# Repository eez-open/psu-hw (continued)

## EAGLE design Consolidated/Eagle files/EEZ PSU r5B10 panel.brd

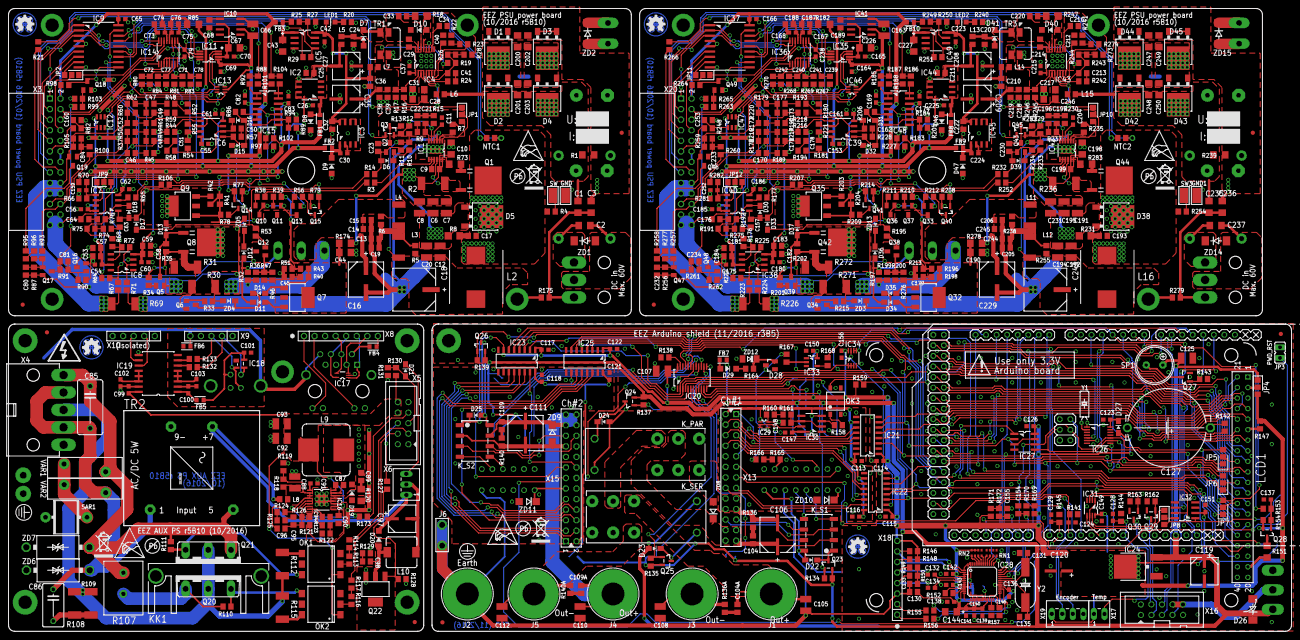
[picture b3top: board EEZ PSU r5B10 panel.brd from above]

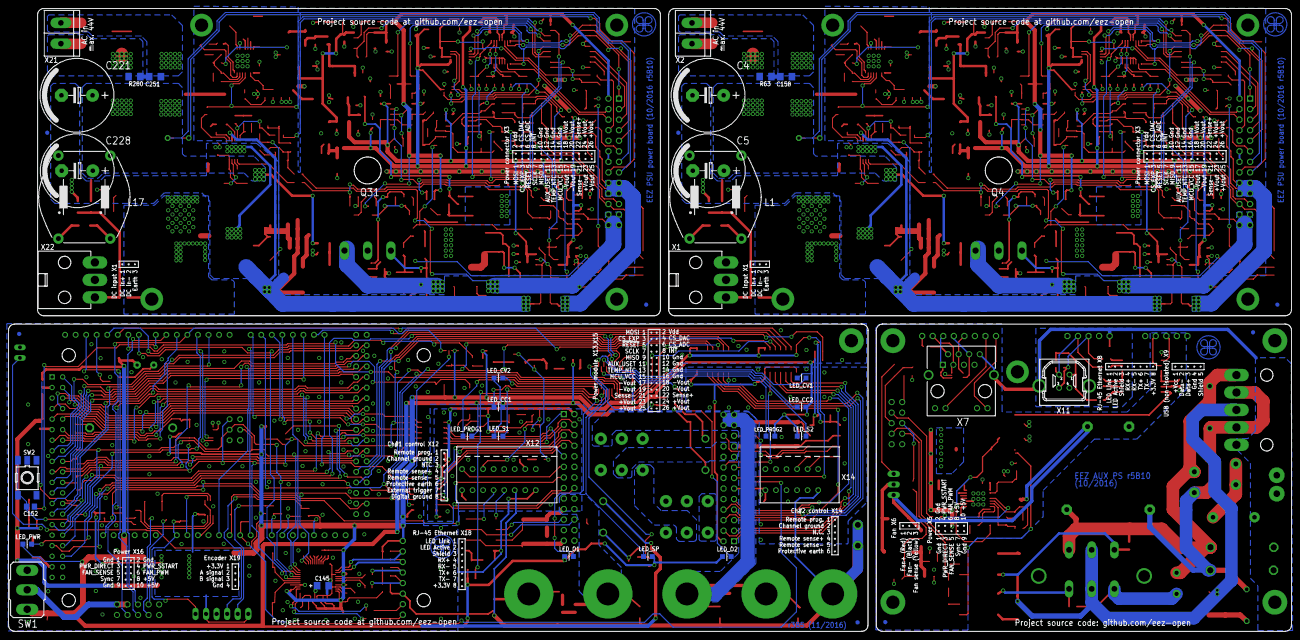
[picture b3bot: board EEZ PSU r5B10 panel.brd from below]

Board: 3 copper layers, 309.0 x 150.0 mm, 839 parts (32 on the bottom side), 579 nets.

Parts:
C1, C2, C3, C235, C236, C237: 4n7; C1206
C4, C5, C221, C228: 2m2; ECAP7.5/18
C6, C7, C8, C88, C92, C93, C191, C195, C231: 4u7; C1210
C9, C25, C32, C104, C109, C199, C211, C222: 470n; C0805
C10, C28, C31, C44, C190, C198, C217, C246: 1u/100V; C1206
C11, C26, C30, C37, C42, C54, C55, C56, C60, C61, C62, C65, C69, C70, C73, C75, C79, C82, C83, C91, C99, C100, C101, C102, C103, C113, C114, C115, C116, C117, C118, C121, C122, C123, C124, C126, C128, C129, C136, C137, C138, C139, C140, C141, C142, C143, C147, C149, C150, C151, C153, C156, C159, C161, C164, C165, C166, C167, C168, C169, C174, C175, C180, C185, C186, C204, C215, C223, C224, C225, C238, C252: 100n; C0603
C12, C20, C66, C107, C125, C163, C192, C194: 10u; C1210
C13, C57, C59, C68, C74, C76, C104A, C109A, C181, C183, C187, C188, C189, C244: 1u; C0805
C14, C15, C19, C39, C96, C160, C205, C206, C218, C245, C253: n.c.; C0805
C16, C229: EEEFK1J470P; CAPAE830X1050N
C17, C33, C89, C193, C220: 330p; C0805
C18, C243: EEEFK1J101P; PANASONIC_F
C21, C50, C162, C197: 120p; C0805
C22, C196: 4n7; C0805
C23, C230: 470p; C0805
C24, C36, C38, C207, C210, C219: 2u2; C0805
C27, C35, C119, C208, C209: 47u; CAPAE660X610N
C29, C87, C90, C130, C214: 22n; C0805
C34, C45, C53, C58, C80, C84, C133, C146, C154, C155, C179, C182, C184, C216, C232, C233: 10n; C0805
C40, C71, C72, C77, C78, C212, C239, C240, C241, C242: 3n3; C0805
C41, C63, C64, C94, C157, C176, C213: 1n; C0805
C43, C145, C227: 4u7; EC1206
C46, C52, C170, C172: 47p; C0805
C47, C48, C49, C51, C81, C171, C173, C177, C178, C234: 2n2; C0805
C67, C144, C226: 10u; EC1206
C85: 6n8 (X1); C102-064X133
C86: 47n/400V; C075-052X106
C95: 3n9; C0805
C97: 220u; CAPAE660X610N
C98, C148, C152: 47n; C0805
C105, C108, C110, C112: 4n7; C1210
C106, C111: EEEFK1J220P; CAPAE830X650N
C120: 10u; PANASONIC_C
C127: EECS5R5H105; SG-R20MM
C131, C135: 18p; C0805
C132, C134: 6n8; C0603
C158, C251: n.c; C1206
C200, C201, C202, C203, C247, C248, C249, C250: 1n; C1206
D1, D2, D3, D4, D42, D43, D44, D45: STPS15H100; TO252@1
D5, D38: STPS15H100; TO252
D6, D11, D12, D13, D14, D15, D16, D17, D18, D21, D22, D23, D24, D25, D27, D30, D31, D32, D33, D34, D35, D36, D37, D39: BAS316; SOD323-W
D7, D10, D19, D40, D41: DFLS1100-7; SOD123
D8, D9, D20, D29, D46, D47: SKL16; SOD123
D26: SMBJ5.0A-TR; DO214AA
D28: BAT54S; SOT23
EEZ_SIGNATURE, EEZ_SIGNATURE1, EEZ_SIGNATURE2, EEZ_SIGNATURE3: SIGNATURESMALL; SIGNATURE_5MM
FB1, FB2, FB3, FB4, FB5, FB6, FB7, FB8, FB9, FB10: 60R@100MHz; BEAD0603
FM1, FM2, FM3, FM4, FM5, FM6, FM7, FM8: FIDUCIAL_2; FIDUCIAL_DUAL
GND, GND1: S1751-46R
IC1, IC42: LTC3864EMSE#PBF; LTC_05-08-1666
IC2, IC44: MC79L05; SOIC127P600X173-8N
IC3, IC45: MC78L05; SOIC127P600X173-8N
IC4, IC43: LM5574MTX/NOPB; SOP65P640X110-16N
IC5, IC49: LP2951SO8; SOIC127P600X175-8N
IC6, IC7, IC39, IC40: TL072D; SOIC127P600X173-8N
IC8, IC38: OP27GSZ; SOIC127P600X173-8N
IC9, IC37: MCP23S08-E/SO; SOIC127P1030X265-18N
IC10, IC41: REF5025AIDG4; SOIC127P600X175-8N
IC11, IC35: DAC8552IDGKTG4; DGK8-M
IC12, IC47: ADG465SOT-23; SOT95P280X145-6N
IC13, IC46: TS5A9411DCKT; SOT65P210X110-6N
IC14, IC36: ADS1120IPWR; PW(R-PDSO-G16)
IC15, IC48: LP339D; SOIC127P600X175-14N
IC16: LM25575MH/NOPB; SOP65P640X110-17N
IC17: TPD4E002DRLR; SOT50P280X60-5N
IC18: TPD2E001DZDR; SOP192P292X122-4N
IC19: ADUM3160BRWZ; SOIC-16W
IC20: TLC5925IDBQR; SOP63P600X175-24N
IC21, IC25: Si8641EC-B-IS1; SOIC-16
IC22, IC23: SI8651EC-B-IS1; SOIC-16
IC24: LD1117ADT33TR; DPACK
IC26: PCA21125T/Q900/1,1; SOP65P640X120-14N
IC27: AT25256B-SSHL-B; SOIC127P600X175-8N
IC28: W5500; TQFP48-7X7
IC29: BC857BS; SOT65P210X110-6N
IC30: TLC555; SOIC127P600X175-8N
IC31: SN74LVC2G08DCTR; SOP65P400X130-8N
IC32: TPS3705-33D; SOIC127P600X175-8N
IC33: SN74LV1T34DBVR; SOT95P280X145-5N
IC34: SN74LVC2G02DCTR; SOP65P400X130-8N
J1, J4: BS-244DSM-R; BP_5_12
J2: BS-244DSM-G; BP_5_12
J3, J5: BS-244DSM-B; BP_5_12
J6: 1-726388-2; PCB_TAB-4.8MM
JP1, JP2, JP4, JP5, JP6, JP7, JP8, JP9, JP10, JP11, JP12: 0R-JUMPA; A0R-JMP
JP3: 901210762; JP1
KK1: SK 145/37,5; SK145
K_PAR: RT424005; RT-C/016A5_ROUND
K_S1, K_S2: G6K-2F-5DC; G6K-2F
K_SER: RT424005; RT-C/016A5_ROUND
L1, L17: RN114-4/02; RN114
L2, L16: 7443551331; WE-HCI_1350/1365
L3, L4, L11, L12: IHLP2020CZER3R3M11; IHLP-2020BZ-11
L5, L6, L7, L8, L13, L14, L15: 2u2; 0805
L9: 100uH; MSS1278
L10: 470u; DE0704
LCD1: TFT_320QVT; LCD_TFT_9341_MIRROR
LED1, LED2: HSMY-C170; LED_0805
LED_CC1, LED_CC2: HSMH-C170; LED_HSMH-C170
LED_CV1, LED_CV2: HSMY-C170; LED_0805
LED_O1, LED_O2: HSMG-C170; LED_0805
LED_PROG1, LED_PROG2: HSMH-C170; LED_HSMH-C170
LED_PWR: HSMD-C170; LED_0805
LED_S1, LED_S2: HSMY-C170; LED_0805
LED_SP: HSMH-C170; LED_HSMH-C170
MCU: Arduino Due; ARDUINO+ICSP_MIRROR
NTC1, NTC2: 10K/Beta:3570K; R_0204/5+0805
OK1: MOC3052; DIL6-SMD
OK2: MOC3062; DIL6-SMD
OK3: HCPL-181
Q1, Q44: IRFR5305; TO229P990X239-3N
Q2, Q10, Q11, Q17, Q36, Q37, Q43, Q47: MMBT5401; SOT23-BEC
Q3, Q15, Q27, Q29, Q30, Q40, Q45: 2N7002; SOT103P240X110-3N
Q4, Q31: IRFP250N; TO247BH-CLR
Q5, Q39: BC857C; SOT23-BEC
Q6, Q34: BC846C; SOT23-BEC
Q7, Q9, Q32, Q35: BCP56-16.115; SOT230P700X180-4N
Q8, Q42: IRFR5410; TO229P990X239-3N
Q12, Q13, Q16, Q18, Q19, Q33, Q38, Q46, Q48, Q49: MMBT5551; SOT23-BEC
Q14, Q41: BSS84P; SOT95P237X112-3N
Q20, Q21: BTA26-600; TOP3S-1
Q22: IRLL014N; SOT223
Q23, Q24, Q25, Q26, Q28: IRLML2246TRPBF; SOT95P237X112-3N
R1, R239: 12K; R1206
R2, R236: R010/2W; R2512
R3, R21, R57, R173, R228, R252, R266: 0R; R0805
R4, R33, R41, R74, R82, R95, R129, R167, R168, R204, R215, R248, R254, R258, R275: 1K; R0805
R5, R6, R43, R127, R164, R196, R238, R255: 100R; R0805
R7, R16, R19, R89, R90, R91, R103, R128, R162, R163, R205, R235, R243, R245, R261, R262, R265: 47K; R0805
R8, R18, R85, R120, R151, R174, R182, R231, R247, R278: 10R; R1206
R9, R10, R22, R23, R29, R45, R52, R54, R61, R75, R76, R78, R86, R98, R99, R106, R125, R131, R147, R153, R157, R170, R172, R180, R181, R189, R190, R191, R192, R206, R207, R209, R233, R237, R241, R251, R263, R264, R274: 10K; R0805
R11, R14, R77, R79, R143, R154, R208, R214, R232, R234: 100K; R0805
R12, R229: 330K; R0805
R13, R175, R253, R279: n.c.; R0805
R15, R102, R134, R135, R137, R139, R141, R144, R145, R169, R171, R183, R230: 4K7; R0805
R17, R32, R34, R35, R37, R46, R62, R65, R68, R94, R96, R110, R111, R119, R122, R124, R176, R177, R178, R179, R184, R197, R201, R202, R246, R276, R277: 2K2; R0805
R20, R40, R53, R195, R198, R240: 470R; R0805
R24, R51, R213, R242: 51K; R0805
R25, R36, R118, R123, R199, R249: 16K; R0805
R26, R92, R97, R104, R121, R130, R185, R186, R227, R244: 5K6; R0805
R27, R70, R88, R101, R165, R166, R187, R188, R250, R282: 5K1; R0805
R28, R56, R126, R138, R159, R212, R273: 1K8; R0805
R30, R271: R080/3W; R2512
R31, R272: 2R2/2W; R2512
R38, R39, R42, R48, R58, R66, R80, R81, R83, R84, R114, R117, R193, R194, R203, R210, R211, R267, R268, R269, R270, R281: 220R; R0805
R44, R55, R216, R221: 7K5 0.1%; R0805
R47, R93, R100, R160, R161, R200, R257, R260: 750R; R0805
R49, R59, R217, R218: 100K 0.1%; R0805
R50, R60, R219, R220: 22K 0.1%; R0805
R63, R280: n.c.; R1206
R64, R72, R222, R225: 2K55 0.1%; R0805
R67, R71, R223, R224: 102R 0.1%; R0805
R69, R226: R020/2W; R2512
R73, R283: 0...10R; R1206
R87, R105, R256, R259: 330R; R0805
R107: 18-22R/7W; R_0913
R108, R109, R112, R115: 330R/2W; R2512
R113, R116, R146, R148, R149, R150: 49R9; R0805
R132, R133: 22R; R0805
R136, R136A, R140, R140A: 1R; R0805
R142, R155, R156, R158: 180R; R0805
R152: 12K4; R0805
RN1, RN2: 4x10K; CAY16
SAR1: CG2-470L; SAR
SH1, SH4: Pgnd to Pout- short; SHORT_NOHOLE
SH2, SH5: Sgnd to Pgnd short; SHORT_NOHOLE
SH3: SHORT_NOHOLE
SP1: LD-BZEN-0903
SW, SW3: S1751-46R
SW1: A101SYCQ04; M9040P
SW2: 1301.9316; TACTM-6XN
TR1, TR3: SRF0703-821M; SRF0703
TR2: VTX-214-005-112 (or MYRRA 47154); PCB_ACDC_MYRRA_5W
U$1, U$2, U$8, U$11: RECYCLE_BIN1/8
U$3, U$5, U$9, U$12: PB_SMALL
U$4, U$6, U$7, U$10: ESD_SYMBOL
VAR1, VAR2: S20K250; VARISTOR
X1, X22: 39303035; MINIFIT_6659-3
X2, X21: 282836-2; TBLOCK5.0_2
X3, X20: SSW-113-02-T-D-RA
X4: 39303055; MINIFIT_6659-5
X5, X16: 09185067324; IDC-10PIN
X6: 22-23-2031
X7: LMJ2138814S0L1T1C; RJ45-VERT
X8: 826629-8; SSW-108-02-S-S
X9, X10: 826629-5; SSW-105-02-S-S
X11: 2411-01; KUSBVX-BS1N
X12: MC000006; MC000006_MIRROR
X13, X15: TSW-113-07-F-D
X14: MC000005; MC000005_MIRROR
X17: 22-23-2021
X18: MC34753; SSW-108-02-S-S
X19: 22-23-2041
Y1: 32,768kHz; R26_XTAL
Y2: 25MHz; HC-49/4H
ZD1, ZD2, ZD14, ZD15: n.c.; DO214AA
ZD3, ZD4: BZX384-C15.115; SOD323-W
ZD5, ZD13: PDZ6.2B; SOD323-W
ZD6, ZD7: 1.5KE400CA; DO201-BIDIR
ZD8, ZD9: P4SMAJ48A; DO214AC
ZD10, ZD11: SMAJ18A; DO214AC
ZD12: 4V3; MINIMELF

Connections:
1V2O: C146.2, IC28.22
!ADC1_SELECT: IC22.4, MCU.15
!ADC2_SELECT: IC25.4, MCU.48
!BP_OE: IC20.21, MCU.10
!BP_OUT0: IC20.5, LED_CV1.C
!BP_OUT1: IC20.6, Q23.1, R134.1
!BP_OUT2: IC20.7, LED_O1.C
!BP_OUT3: IC20.8, LED_SP.C
!BP_OUT4: IC20.9, LED_PROG1.C
!BP_OUT5: IC20.10, LED_S1.C
!BP_OUT6: IC20.11, LED_CC1.C
!BP_OUT7: IC20.12, LED_CV2.C
!BP_OUT8: IC20.13, Q25.1, R135.1
!BP_OUT9: IC20.14, Q24.1, R137.1
!BP_OUT10: IC20.15, LED_CC2.C
!BP_OUT12: IC20.17, LED_S2.C
!BP_OUT13: IC20.18, LED_O2.C
!BP_OUT14: IC20.19, Q26.1, R139.1
!BP_OUT15: IC20.20, LED_PWR.C
!CH1_ADC: IC22.13, X13.6
!CH1_DAC: IC21.12, X13.4
!CH1_EXPANDER: IC21.13, X13.3
!CH1_INT: IC22.11, X13.8
!CH1_RESET: IC22.14, X13.5
!CH2_ADC: IC25.13, X15.6
!CH2_DAC: IC23.12, X15.4
!CH2_EXPANDER: IC23.13, X15.3
!CH2_INT: IC23.11, X15.8
!CH2_RESET: IC25.14, X15.5
!CONVEND1: IC22.6, MCU.21
!CONVEND2: IC23.6, MCU.20
!DAC1_SELECT: IC21.5, MCU.16
!DAC2_SELECT: IC23.5, MCU.47
!DP_DRIVE: Q9.1, R41.1, R78.1
!DP_DRIVE1: Q35.1, R204.1, R209.1
!EEPROM_SELECT: IC27.1, MCU.49
!ETH_IRQ: IC28.36, MCU.18
!ETH_SELECT: IC28.32, MCU.11
!INT: JP2.2, X3.8
!INT1: JP11.2, X20.8
!IO_EXPANDER1: IC21.4, MCU.17
!IO_EXPANDER2: IC23.4, MCU.46
!MR: C152.2, IC32.1, JP8.1, SW2.3, SW2.4
!PS_DRDY: IC14.14, JP2.3
!PS_DRDY1: IC36.14, JP11.3
!PS_RESET: IC9.6, X3.5
!PS_RESET1: IC37.6, X20.5
!RESET: IC22.3, IC25.3, IC28.37, IC32.7, MCU.RESET
!RESET1: IC31.1, IC31.6, JP8.3
!RTC_IRQ: IC26.5, MCU.19
!SET_100%: IC9.13, Q3.1
!SET_100%1: IC37.13, Q45.1
!SET_DP: IC9.11, Q14.1, R77.2
!SET_DP1: IC37.11, Q41.1, R214.2
+3V3: C107.1, C114.1, C115.1, C117.1, C120.1, C122.1, C126.1, C130.1, C136.2, C138.1, C139.1, C140.1, C141.1, C142.1, C143.1, C144.+, C149.2, C150.1, C151.2, C156.1, D27.A, IC20.24, IC21.1, IC22.1, IC22.7, IC23.1, IC23.7, IC24.4, IC25.1, IC27.3, IC27.7, IC27.8, IC28.4, IC28.8, IC28.11, IC28.15, IC28.17, IC28.21, IC28.28, IC31.8, IC32.2, IC33.5, IC34.8, JP4.3, Q28.2, R146.1, R147.2, R148.2, R154.2, R159.1, R169.1, R171.1, RN2.6, RN2.7, RN2.8, X13.15, X15.15, X17.1, X18.8, X19.1
+5V: C65.1, C73.2, C74.2, C92.1, C93.1, C99.1, FB3.P$2, IC9.18, IC14.13, IC16.11, IC19.16, L9.2, OK1.1, OK2.1, Q13.B, Q14.2, R77.1, R88.2, R98.2, R101.2, R121.1, R130.1, X3.2, X5.8, X5.10
+5V1: C166.1, C168.2, C188.2, FB10.P$2, IC36.13, IC37.18, Q33.B, Q41.2, R187.2, R188.2, R214.1, R264.2, X20.2
+5V2: C119.1, C125.2, D26.C, FB7.P$1, IC24.3, JP4.1, LED_CC1.A, LED_CC2.A, LED_CV1.A, LED_CV2.A, LED_O1.A, LED_O2.A, LED_PROG1.A, LED_PROG2.A, LED_PWR.A, LED_S1.A, LED_S2.A, LED_SP.A, MCU.5V, Q23.2, Q24.2, Q25.2, Q26.2, R134.2, R135.2, R137.2, R139.2, SP1.+B, SW1.3
+VNR: C32.1, C36.1, C42.1, IC3.8, IC5.8, L7.2, LED1.A
+VNR1: C210.1, C222.1, C223.1, IC45.8, IC49.8, L14.2, LED2.A
+VREF: C67.+, C70.2, C79.2, IC10.6, IC11.2, IC14.9, R70.1
+VREF1: C165.2, C226.+, C238.2, IC35.2, IC36.9, IC41.6, R282.1
-9V: C25.2, C27.2, IC2.2, IC2.3, IC2.6, IC2.7, L5.2, R41.2, R42.2
-9V1: C208.2, C211.2, IC44.2, IC44.3, IC44.6, IC44.7, L13.2, R203.2, R204.2
AC_EARTH: FB6.P$1, SAR1.P$2, X4.5, X7.8, X7.SH1, X7.SH2, X9.5, X11.M1, X11.M2, ZD6.C, ZD7.C
AC_IN1: C202.1, C203.2, D3.3, D4.1, D4.2, R63.2, X2.1, ZD2.A
AC_IN1_MAIN: C85.1, Q21.A1, R107.1, R111.2, TR2.5, VAR1.P$2, X4.1, ZD7.A
AC_IN2: C158.1, C200.1, C201.2, D1.3, D2.1, D2.2, X2.2, ZD2.C
AC_IN2_MAIN: C85.2, C86.1, TR2.1, VAR2.P$1, X4.2, X4.4, ZD6.A
AC_IN3: C247.1, C248.2, C251.1, D42.1, D42.2, D44.3, X21.2, ZD15.C
AC_IN4: C249.1, C250.2, D43.1, D43.2, D45.3, R280.2, X21.1, ZD15.A
AUX1_USET_IN: X12.8, X12.8.1, X13.11, ZD10.C
AUX2_USET_IN: X14.6, X14.6.1, X15.11, ZD11.C
AUX_+3V3: FB4.P$2, X8.8
AUX_ETH_ACTLED: X7.10, X8.2
AUX_ETH_IN+: IC17.4, X7.4, X8.4
AUX_ETH_IN-: IC17.5, X7.6, X8.5
AUX_ETH_LINKLED: X7.12, X8.1
AUX_ETH_OUT+: IC17.1, X7.1, X8.6
AUX_ETH_OUT-: IC17.3, X7.3, X8.7
AUX_FAN_CTRL: R127.2, X5.6
AUX_FAN_SENSE: D21.A, R130.2, R131.1, X5.5
AUX_PWR_DIRECT: R114.2, X5.3
AUX_PWR_SSTART: R117.2, X5.4
AUX_USET_IN: R82.2, X3.11
AUX_USET_IN1: R248.2, X20.11
AUX_USET_SW: IC9.14, IC13.1
AUX_USET_SW1: IC37.14, IC46.1
BATT_NTC: MCU.A4, OK3.4, R159.2
BP_SELECT: IC20.4, MCU.9
BUZZER: MCU.12, Q27.1, R143.2
CC_ACTIVE: IC9.12, R101.1, R104.2
CC_ACTIVE1: IC37.12, R186.2, R188.1
CH1_GND: C113.2, C116.2, C147.2, C148.1, IC21.9, IC21.15, IC22.9, IC30.1, OK3.2, X12.7, X12.7.1, X13.10, X13.12, X13.14, ZD10.A
CH1_MISO: IC21.11, X13.9
CH1_MOSI: IC21.14, X13.1
CH1_SCLK: IC22.12, X13.7
CH1_SYNC: IC22.15, X13.16
CH1_VDD: C113.1, C116.1, C147.1, IC21.10, IC21.16, IC22.10, IC22.16, IC29.1, IC29.4, IC30.4, IC30.8, X13.2
CH2_GND: C118.2, C121.2, IC23.9, IC25.9, IC25.15, X14.5, X14.5.1, X15.10, X15.12, X15.14, ZD11.A
CH2_MISO: IC25.11, X15.9
CH2_MOSI: IC23.14, X15.1
CH2_SCLK: IC25.12, X15.7
CH2_SYNC: IC23.15, X15.16
CH2_VDD: C118.1, C121.1, IC23.10, IC23.16, IC25.10, IC25.16, X15.2
CS_ADC: IC14.2, X3.6
CS_ADC1: IC36.2, X20.6
CS_DAC: IC11.5, X3.4
CS_DAC1: IC35.5, X20.4
CS_EXPANDER: IC9.7, X3.3
CS_EXPANDER1: IC37.7, X20.3
CV_ACTIVE: IC9.15, R88.1, R92.2
CV_ACTIVE1: IC37.15, R185.2, R187.1
D+: IC18.2, R133.1, X9.3, X11.3
D-: IC18.3, R132.1, X9.2, X11.2
DC+: C2.2, L1.2, X1.1, ZD1.C
DC+1: C237.2, L17.2, X22.1, ZD14.C
DC-: C2.1, L1.1, X1.2, ZD1.A
DC-1: C237.1, L17.1, X22.2, ZD14.A
DC_BIAS: C44.1, Q7.2, Q7.4, R38.2, R39.2, R174.2
DC_BIAS1: C190.1, Q32.2, Q32.4, R210.2, R211.2, R278.2
DC_OUT: C1.2, C4.+, C5.+, C6.1, C7.1, C8.1, C9.2, C10.1, C201.1, C203.1, D2.3, D4.3, IC1.11, L1.3, L6.1, R1.1, R2.1, R174.1
DC_OUT1: C191.1, C195.1, C198.1, C199.2, C221.+, C228.+, C231.1, C235.2, C248.1, C250.1, D42.3, D43.3, IC42.11, L15.1, L17.3, R236.1, R239.1, R278.1
DC_PREG1: C28.1, C31.1, IC4.3, L6.2, R16.2
DC_PREG2: C88.1, IC16.3, L8.2, R118.2
DC_PREG3: C217.1, C246.1, IC43.3, L15.2, R245.2
DP_LED: Q14.3, R78.2
DP_LED1: Q41.3, R209.2
EARTH: C1.1, C3.2, R175.2, X1.3
EARTH1: C235.1, C236.2, R279.2, X22.3
EARTH2: C105.2, C108.1, C110.2, C112.1, C130.2, C133.2, J2.P$1, J6.P$1, J6.P$2, X12.3, X12.3.1, X14.1, X14.1.1, X18.3
ENC_A: C154.2, MCU.A8, R170.1
ENC_B: C155.1, MCU.A9, R172.1
ETH_ACTLED: IC28.27, R155.1
ETH_IN+: C134.1, R150.1, X18.4
ETH_IN-: C132.1, R149.2, X18.5
ETH_LINKLED: IC28.25, R156.1
ETH_OUT+: IC28.2, R148.1, X18.6
ETH_OUT-: IC28.1, R146.2, X18.7
EXT_TRIG: MCU.A7, R168.1
FAN_OUT: C98.2, D20.A, L10.2, Q22.2, Q22.4
FAN_PWM: MCU.6, X16.6
FAN_SENSE: MCU.13, X16.5
FB: IC1.5, Q3.2, R12.2, R13.2, R15.1
FB1: IC42.5, Q45.2, R229.2, R230.1, R253.2
GCOM: JP9.2, R44.1, R64.1
GCOM1: JP12.2, R216.1, R222.1
GND: C3.1, C4.-, C5.-, C6.2, C7.2, C8.2, C10.2, C12.2, C18.2, C20.2, C24.2, C25.1, C26.1, C27.1, C28.2, C30.2, C31.2, C32.2, C34.2, C35.2, C36.2, C37.1, C38.2, C39.2, C40.1, C42.2, C43.-, C44.2, C45.2, C53.1, C54.2, C55.1, C56.1, C57.1, C58.1, C59.1, C60.2, C61.1, C62.1, C65.2, C66.2, C67.-, C68.2, C69.1, C70.1, C71.1, C72.2, C73.1, C74.1, C75.1, C76.1, C77.1, C78.1, C79.1, C82.1, C83.1, C88.2, C90.2, C91.1, C92.2, C93.2, C94.1, C99.2, C102.2, C159.2, C160.1, C200.2, C202.2, D1.1, D1.2, D3.1, D3.2, D5.1, D5.2, D8.C, D9.A, GND.P$1, IC1.TP, IC2.5, IC3.2, IC3.3, IC3.6, IC3.7, IC4.9, IC4.12, IC5.4, IC9.4, IC9.5, IC9.9, IC10.4, IC11.8, IC13.3, IC14.3, IC14.4, IC14.5, IC14.8, IC16.9, IC16.12, IC16.TP, IC17.2, IC19.9, IC19.15, JP9.3, L1.4, Q8.2, Q15.2, Q16.E, Q18.E, Q22.3, R1.2, R8.1, R17.1, R20.2, R22.2, R27.2, R28.1, R46.1, R47.1, R51.1, R66.2, R79.1, R90.1, R94.1, R97.2, R103.1, R119.1, R122.2, R126.2, R128.1, R129.1, R131.2, SH1.P$2, SH2.P$2, TR1.4, TR2.9, X3.10, X3.12, X3.14, X5.1, X5.2, X5.9, X7.9, X7.11, X10.4
GND1: C153.1, C161.1, C163.2, C164.1, C165.1, C166.2, C167.1, C168.1, C169.1, C174.1, C175.2, C179.2, C180.2, C181.1, C182.1, C183.1, C184.1, C185.1, C186.1, C187.1, C188.1, C189.2, C190.2, C191.2, C192.2, C194.2, C195.2, C198.2, C207.2, C208.1, C209.2, C210.2, C211.1, C212.1, C215.1, C216.2, C217.2, C218.2, C219.2, C221.-, C222.2, C223.2, C224.2, C225.1, C226.-, C227.-, C228.-, C231.2, C236.1, C238.1, C239.1, C240.1, C241.1, C242.2, C243.2, C246.2, C247.2, C249.2, C252.2, C253.1, D38.1, D38.2, D44.1, D44.2, D45.1, D45.2, D46.C, D47.A, GND1.P$1, IC35.8, IC36.3, IC36.4, IC36.5, IC36.8, IC37.4, IC37.5, IC37.9, IC41.4, IC42.TP, IC43.9, IC43.12, IC44.5, IC45.2, IC45.3, IC45.6, IC45.7, IC46.3, IC49.4, JP12.3, L17.4, Q40.2, Q42.2, Q48.E, Q49.E, R184.1, R200.1, R208.1, R213.1, R227.2, R231.1, R239.2, R240.2, R241.2, R246.1, R250.2, R262.1, R265.1, R273.1, R276.1, R281.2, SH4.P$2, SH5.P$2, TR3.4, X20.10, X20.12, X20.14
GND7: C107.2, C114.2, C115.2, C117.2, C119.2, C120.2, C122.2, C123.1, C124.1, C125.1, C126.2, C127.2, C128.1, C129.1, C131.2, C135.2, C136.1, C137.1, C138.2, C139.2, C140.2, C141.2, C142.2, C143.2, C144.-, C146.1, C149.1, C150.2, C151.1, C152.1, C154.1, C155.2, C156.2, D22.A, D23.A, D24.A, D25.A, D26.A, D28.1, IC20.1, IC21.2, IC21.8, IC22.8, IC23.8, IC24.1, IC25.2, IC25.8, IC26.7, IC27.4, IC28.29, IC31.4, IC32.3, IC32.4, IC33.3, IC34.4, JP3.2, K_PAR.A1, K_S1.8, K_S2.8, K_SER.A1, LCD1.1, MCU.GND, MCU.GND1, MCU.GND2, MCU.GND3, MCU.GND4, MCU.ICSP_GND, OK3.3, Q27.2, Q29.2, Q30.2, R138.1, R141.2, R143.1, R144.2, R145.2, R157.1, R162.2, R163.2, RN1.5, RN1.6, RN1.7, RN1.8, RN2.5, SH3.P$1, SW2.1, SW2.2, SW2.5, X12.1, X12.1.1, X16.1, X16.2, X16.9, X19.4, ZD12.A
GNDA: C145.-, IC28.3, IC28.9, IC28.14, IC28.16, IC28.19, IC28.48, R152.1, SH3.P$2
INT_EXP: IC9.8, JP2.1
INT_EXP1: IC37.8, JP11.1
IS: D10.A, IC4.13, R18.1
IS1: D19.A, IC16.13, R120.1
IS2: D40.A, IC43.13, R247.1
ISENSE+: IC8.3, R64.2, R67.2
ISENSE+1: IC38.3, R222.2, R223.2
ISENSE-: IC8.2, R71.2, R72.1
ISENSE-1: IC38.2, R224.2, R225.1
ISOLATOR1_EN: IC21.7, MCU.14
ISOLATOR2_EN: IC25.7, MCU.45
I_MON: IC8.6, R68.1, R72.2, R84.1
I_MON1: IC38.6, R176.1, R225.2, R268.1
I_SERVO: C63.2, D17.C, D18.A, IC7.1, R106.1
I_SERVO1: C157.2, D30.A, D33.C, IC40.1, R207.1
I_SET: IC11.3, R65.1, R80.1
I_SET1: IC35.3, R177.1, R270.1
LCDSD_CS: LCD1.38, MCU.53
LCD_BRIGHTNESS: MCU.7, R153.1
LCD_CS: LCD1.15, MCU.39
LCD_DB0: LCD1.21, MCU.37
LCD_DB1: LCD1.22, MCU.36
LCD_DB2: LCD1.23, MCU.35
LCD_DB3: LCD1.24, MCU.34
LCD_DB4: LCD1.25, MCU.33
LCD_DB5: LCD1.26, MCU.32
LCD_DB6: LCD1.27, MCU.31
LCD_DB7: LCD1.28, MCU.30
LCD_DB8: LCD1.7, MCU.22
LCD_DB9: LCD1.8, MCU.23
LCD_DB10: LCD1.9, MCU.24
LCD_DB11: LCD1.10, MCU.25
LCD_DB12: LCD1.11, MCU.26
LCD_DB13: LCD1.12, MCU.27
LCD_DB14: LCD1.13, MCU.28
LCD_DB15: LCD1.14, MCU.29
LCD_RD: LCD1.6, R147.1
LCD_RESET: LCD1.17, MCU.38
LCD_RS: LCD1.4, MCU.41
LCD_WR: LCD1.5, MCU.40
LED_A: LCD1.19, R151.2
L_OUT: C12.1, C18.1, C20.1, L2.2, L3.1, R5.1, R10.1, R11.1, R12.1
L_OUT12: C192.1, C194.1, C243.1, L12.1, L16.2, R229.1, R233.1, R234.1, R255.1
MCU_D+: IC19.10, X10.3
MCU_D-: IC19.11, X10.2
MCU_VCC: NTC1.2, NTC1.2.1, X3.15
MCU_VCC1: NTC2.2, NTC2.2.1, X20.15
MISO: IC21.6, IC25.6, IC26.8, IC27.2, IC28.34, JP7.1, LCD1.35, MCU.ICSP_MISO
MODE: IC1.1, JP1.2
MODE1: IC42.1, JP10.2
MOSI: IC20.2, IC21.3, IC23.3, IC26.9, IC27.5, IC28.35, JP6.1, LCD1.37, MCU.ICSP_MOSI
unnamed: Q9.3, R42.1
unnamed: Q5.B, R34.2
unnamed: C46.2, R45.1
unnamed: C26.2, D8.A, FB1.P$1, IC2.1
unnamed: C30.1, D9.C, FB2.P$1, IC3.1
unnamed: C43.+, FB3.P$1, IC5.1, R25.1, R29.1
unnamed: R4.2, SW.P$1
unnamed: R74.2, R75.1
unnamed: IC12.4, IC13.6
unnamed: C52.2, R61.1
unnamed: C68.1, IC10.5
unnamed: C160.2, IC12.1, R82.1
unnamed: C63.1, R74.1
unnamed: C158.2, R63.1
unnamed: C159.1, IC7.5, R66.1, R70.2
unnamed: IC7.6, IC7.7, JP9.1
unnamed: C49.1, R59.2, R60.1
unnamed: C50.2, R57.1
unnamed: D6.C, Q2.E, R10.2
unnamed: C21.1, IC1.6, R9.2
unnamed: C22.1, R9.1
unnamed: C64.2, R76.1
unnamed: C9.1, IC1.9
unnamed: R21.2, X3.16
unnamed: C80.2, Q17.B, R87.1, R93.2, R96.2
unnamed: C47.2, R48.1
unnamed: C51.2, R58.1
unnamed: C78.2, IC14.10, R83.2
unnamed: IC6.3, R48.2, R52.2
unnamed: IC1.12, R73.1
unnamed: IC1.2, R7.1
unnamed: C50.1, D16.C, IC6.2, R54.2, R58.2
unnamed: C11.2, IC1.4
unnamed: C23.1, Q2.C, Q3.3, R13.1
unnamed: C13.1, C19.2, L3.2, L4.1, R5.2, R6.1
unnamed: IC1.8, R3.1
unnamed: D18.C, IC7.2, R68.2, R75.2, R76.2
unnamed: C17.2, R8.2
unnamed: Q18.B, R99.1, R103.2
unnamed: C81.2, Q17.C, R91.1, R99.2
unnamed: C71.2, IC14.11, R81.2
unnamed: C75.2, C76.2, IC14.12, R85.2
unnamed: LED1.C, R20.1
unnamed: Q12.B, R36.1, R46.2, R47.2
unnamed: IC15.1, IC15.2, R92.1
unnamed: C33.2, R18.2
unnamed: Q19.C, R95.1
unnamed: IC15.13, IC15.14, R104.1
unnamed: C84.1, Q19.B, R100.1, R105.2
unnamed: IC7.3, R65.2
unnamed: C72.1, IC14.6, R80.2
unnamed: C95.2, R125.2
unnamed: C81.1, Q16.B, R90.2, R91.2
unnamed: D15.A, D17.A, R53.1
unnamed: C77.2, IC14.7, R84.2
unnamed: D11.C, D12.A, Q4.G, R32.1
unnamed: C95.1, C96.1, IC16.6, R121.2, R126.1
unnamed: C87.2, IC16.16
unnamed: C96.2, IC16.5, R124.1
unnamed: IC16.7, R123.1
unnamed: C91.2, IC16.1
unnamed: D11.A, Q7.3
unnamed: C94.2, IC16.8
unnamed: IC5.7, R25.2, R27.1
unnamed: D14.A, Q7.1, R40.2, R43.1
unnamed: C90.1, IC16.10
unnamed: C45.1, R40.1
unnamed: R173.1, X5.7
unnamed: IC16.2, R118.1, R119.2
unnamed: C89.2, R120.2
unnamed: OK1.6, Q21.G, R111.1
unnamed: OK2.4, Q20.G, R110.2
unnamed: OK2.6, R115.1
unnamed: R113.2, R114.1
unnamed: R116.2, R117.1
unnamed: OK1.4, R112.1
unnamed: C41.2, R24.2
unnamed: R26.2, R28.2
unnamed: C23.2, D6.A, Q2.B, R11.2, R14.1
unnamed: R22.1, R23.2
unnamed: Q20.A2, Q21.A2, R108.1, R109.1, R112.2, R115.2, X4.3
unnamed: IC31.7, Q29.1, R162.1
unnamed: C86.2, R108.2, R109.2
unnamed: C98.1, R129.2
unnamed: Q22.1, R127.1, R128.2
unnamed: C97.2, L10.1, X6.2
unnamed: C103.1, IC19.3, IC19.4, IC19.5
unnamed: IC19.6, R132.2
unnamed: IC19.7, R133.2
unnamed: C100.1, FB5.P$2, IC19.1
unnamed: C102.1, IC19.12, IC19.13, IC19.14
unnamed: D22.C, K_S1.1, Q23.3
unnamed: D25.C, K_S2.1, Q26.3
unnamed: C104.2, R136.2
unnamed: C109.2, R140.2
unnamed: IC20.16, LED_PROG2.C
unnamed: K_SER.14A, K_SER.14B
unnamed: K_PAR.12A, K_SER.11B
unnamed: K_PAR.12B, K_SER.11A
unnamed: SW1.2, X16.8, X16.10
unnamed: Q27.3, SP1.-B
unnamed: JP4.2, LCD1.2
unnamed: Q28.3, R151.1
unnamed: JP7.2, LCD1.33
unnamed: JP5.2, LCD1.29
unnamed: JP6.2, LCD1.31
unnamed: C127.1, R142.1
unnamed: IC28.23, R157.2
unnamed: C123.2, D27.C, IC26.14, R142.2
unnamed: IC28.10, R152.2
unnamed: C131.1, IC28.31, Y2.1
unnamed: C135.1, IC28.30, Y2.2
unnamed: C132.2, IC28.5
unnamed: SAR1.P$1, VAR1.P$1, VAR2.P$2
unnamed: C134.2, IC28.6
unnamed: R156.2, X18.1
unnamed: C48.1, R49.2, R50.1
unnamed: R155.2, X18.2
unnamed: IC28.43, RN2.3
unnamed: IC28.44, RN2.2
unnamed: IC28.45, RN2.1
unnamed: IC28.42, RN2.4
unnamed: IC28.38, RN1.4
unnamed: C133.1, R149.1, R150.2
unnamed: FB4.P$1, X7.2
unnamed: IC28.39, RN1.3
unnamed: IC28.41, RN1.1
unnamed: C41.1, IC4.6, R19.2, R26.1
unnamed: D14.C, Q6.C, ZD4.C
unnamed: IC28.40, RN1.2
unnamed: C29.2, IC4.16
unnamed: C137.2, Q28.1, R153.2, R154.1
unnamed: IC26.1, Y1.2
unnamed: IC26.2, Y1.1
unnamed: IC4.5, R24.1
unnamed: C148.2, IC30.2, IC30.6, R161.2
unnamed: IC29.6, IC30.7, R160.1
unnamed: OK3.1, R158.2
unnamed: D28.3, R166.1, R167.2
unnamed: IC33.2, R167.1
unnamed: IC33.4, R168.2
unnamed: R165.2, X12.2, X12.2.1
unnamed: D12.C, ZD5.C
unnamed: D28.2, R164.1, ZD12.C
unnamed: Q12.E, R53.2
unnamed: Q8.3, R31.1, R34.1, R35.1
unnamed: D13.A, Q5.C, Q8.1, R35.2
unnamed: D29.C, R164.2
unnamed: D29.A, FB7.P$2
unnamed: IC6.5, R44.2, R45.2, R49.1
unnamed: IC32.8, JP8.2
unnamed: Q20.A1, R107.2, R110.1
unnamed: IC15.5, IC15.6, R86.2
unnamed: IC31.3, Q30.1, R163.1
unnamed: D23.C, K_SER.A2, Q25.3
unnamed: D24.C, K_PAR.A2, Q24.3
unnamed: JP3.1, MCU.A12
unnamed: IC6.6, R55.2, R59.1, R61.2
unnamed: Q1.1, R73.2
unnamed: IC15.8, IC15.11, R106.2
unnamed: D21.C, X6.3
unnamed: R165.1, R166.2
unnamed: IC4.7, R23.1
unnamed: C37.2, IC4.1
unnamed: C40.2, IC4.8
unnamed: C34.1, IC4.10
unnamed: R122.1, R123.2
unnamed: IC15.7, IC15.9, R89.1, R94.2
unnamed: R124.2, R125.1
unnamed: R160.2, R161.1
unnamed: R95.2, R96.1
unnamed: OK2.2, R116.1
unnamed: OK1.2, R113.1
unnamed: C104A.2, R136A.2
unnamed: IC15.4, IC15.10, R97.1, R102.2
unnamed: C109A.2, R140A.2
unnamed: C24.1, D7.A, L5.1
unnamed: IC4.2, R16.1, R17.2
unnamed: IC16.4, R173.2
unnamed: Q11.E, R39.1
unnamed: Q10.E, R38.1
unnamed: R169.2, R170.2, X19.2
unnamed: Q13.E, R56.2
unnamed: R171.2, R172.2, X19.3
unnamed: IC40.3, R177.2
unnamed: IC39.3, R180.2, R193.2
unnamed: C162.1, D31.C, IC39.2, R181.2, R194.2
unnamed: C167.2, C187.2, IC36.12, R182.2
unnamed: IC48.1, IC48.2, R185.1
unnamed: IC39.5, R189.2, R216.2, R217.1
unnamed: IC39.6, R190.2, R218.1, R221.2
unnamed: C173.1, R218.2, R220.1
unnamed: C171.1, R217.2, R219.1
unnamed: C170.2, R189.1
unnamed: C172.2, R190.1
unnamed: C176.2, R192.1
unnamed: D30.C, IC40.2, R176.2, R191.2, R192.2
unnamed: Q6.B, R33.1
unnamed: C177.2, R193.1
unnamed: C178.2, R194.1
unnamed: D32.A, D33.A, R195.1
unnamed: D34.C, D36.A, Q31.G, R197.1
unnamed: D34.A, Q32.3
unnamed: D35.A, Q32.1, R196.1, R198.2
unnamed: D35.C, Q34.C, ZD3.C
unnamed: C179.1, R198.1
unnamed: D36.C, ZD13.C
unnamed: Q42.3, R201.1, R202.1, R272.1
unnamed: D37.A, Q39.C, Q42.1, R202.2
unnamed: Q38.E, R195.2
unnamed: IC48.13, IC48.14, R186.1
unnamed: IC48.5, IC48.6, R206.2
unnamed: IC48.8, IC48.11, R207.2
unnamed: IC48.7, IC48.9, R184.2, R205.1
unnamed: IC48.4, IC48.10, R183.2, R227.1
unnamed: Q37.E, R210.1
unnamed: Q36.E, R211.1
unnamed: Q33.E, R212.2
unnamed: Q38.B, R199.1, R200.2, R276.2
unnamed: Q34.B, R215.1
unnamed: Q35.3, R203.1
unnamed: Q39.B, R201.2
unnamed: C189.1, IC41.5
unnamed: IC40.6, IC40.7, JP12.1
unnamed: C162.2, R228.1
unnamed: C193.2, R231.2
unnamed: C230.2, D39.A, Q43.B, R232.1, R234.2
unnamed: D39.C, Q43.E, R233.2
unnamed: C197.1, IC42.6, R237.2
unnamed: C196.1, R237.1
unnamed: C199.1, IC42.9
unnamed: IC42.12, R283.1
unnamed: IC42.2, R235.1
unnamed: C204.2, IC42.4
unnamed: C230.1, Q43.C, Q45.3, R253.1
unnamed: C205.2, C244.1, L11.1, L12.2, R238.1, R255.2
unnamed: C207.1, D41.A, L13.1
unnamed: LED2.C, R240.1
unnamed: C213.2, R242.2
unnamed: C213.1, IC43.6, R243.2, R244.1
unnamed: C214.2, IC43.16
unnamed: IC43.5, R242.1
unnamed: IC43.7, R274.1
unnamed: C215.2, IC43.1
unnamed: C212.2, IC43.8
unnamed: C216.1, IC43.10
unnamed: IC43.2, R245.1, R246.2
unnamed: C220.2, R247.2
unnamed: C225.2, D46.A, FB8.P$1, IC44.1
unnamed: C224.1, D47.C, FB9.P$1, IC45.1
unnamed: IC46.6, IC47.4
unnamed: C253.2, IC47.1, R248.1
unnamed: IC49.7, R249.2, R250.1
unnamed: IC42.8, R252.1
unnamed: R254.2, SW3.P$1
unnamed: C232.2, Q47.B, R256.1, R257.2, R277.2
unnamed: C234.2, Q47.C, R261.1, R263.2
unnamed: Q46.C, R258.1
unnamed: C233.1, Q46.B, R259.2, R260.1
unnamed: C234.1, Q48.B, R261.2, R262.2
unnamed: Q49.B, R263.1, R265.2
unnamed: C227.+, FB10.P$1, IC49.1, R249.1, R251.1
unnamed: R266.2, X20.16
unnamed: C239.2, IC36.10, R267.2
unnamed: C240.2, IC36.7, R268.2
unnamed: C241.2, IC36.11, R269.2
unnamed: C242.1, IC36.6, R270.2
unnamed: R191.1, R275.2
unnamed: C157.1, R275.1
unnamed: R244.2, R273.2
unnamed: R241.1, R274.2
unnamed: R258.2, R277.1
unnamed: C251.2, R280.1
unnamed: C252.1, IC40.5, R281.1, R282.2
unnamed: Q44.1, R283.2
unnamed: IC20.23, R138.2
NTC1: C124.2, MCU.A5, R141.1, X13.13
NTC2: C129.2, MCU.A6, R145.1, X15.13
NTC_IN: IC29.2, IC29.3, IC29.5, X12.6, X12.6.1
OUT1+: C104A.1, C105.1, J1.P$1, K_SER.12B
OUT1-: C106.2, C108.2, J3.P$1, K_PAR.14B, K_S1.7, R136.1, R136A.1, X13.17, X13.18, X13.19, X13.20, ZD8.A
OUT2+: C109.1, C109A.1, C110.1, C111.1, J4.P$1, K_PAR.14A, K_S2.7, X15.23, X15.24, X15.25, X15.26, ZD9.C
OUT2-: C112.2, J5.P$1, K_SER.12A, R140A.1
OUT+: C48.2, C51.1, C64.1, C80.1, Q5.E, Q6.E, Q17.E, R14.2, R30.2, R31.2, R37.1, R87.2, X3.23, X3.24, X3.25, X3.26
OUT+1: C171.2, C176.1, C178.1, C232.1, Q34.E, Q39.E, Q47.E, R178.1, R232.2, R256.2, R271.2, R272.2, X20.23, X20.24, X20.25, X20.26
OUT-: C47.1, C49.2, C84.2, Q19.E, R62.2, R67.1, R69.1, R105.1, X3.17, X3.18, X3.19, X3.20
OUT-1: C173.2, C177.1, C233.2, Q46.E, R179.2, R223.1, R226.1, R259.1, X20.17, X20.18, X20.19, X20.20
POST_OE: Q15.3, R56.1
POST_OE1: Q40.3, R212.1
POUT-: C13.2, C14.2, C15.2, C16.2, C19.1, R69.2, R71.1, SH1.P$1
POUT-1: C205.1, C206.2, C229.2, C244.2, C245.2, R224.1, R226.2, SH4.P$1
PREG_OUT: C14.1, C15.1, C16.1, L4.2, Q4.D, R6.2
PREG_OUT1: C206.1, C229.1, C245.1, L11.2, Q31.D, R238.2
PRE_OE: IC9.17, Q15.1, R3.2, R79.2
PRE_OE1: IC37.17, Q40.1, R208.2, R252.2
PS_MISO: IC9.3, IC14.15, X3.9
PS_MISO1: IC36.15, IC37.3, X20.9
PS_MOSI: IC9.2, IC11.7, IC14.16, X3.1
PS_MOSI1: IC35.7, IC36.16, IC37.2, X20.1
PS_SCLK: IC9.1, IC11.6, IC14.1, X3.7
PS_SCLK1: IC35.6, IC36.1, IC37.1, X20.7
PWRDIR: IC31.2, MCU.A1
PWRGOOD: IC5.5, IC9.16, R29.2
PWRGOOD1: IC37.16, IC49.5, R251.2
PWRSS: IC31.5, MCU.A2
PWR_DIRECT: Q29.3, X16.3
PWR_IN1+: C104.1, C106.1, K_PAR.11A, K_S1.2, X13.23, X13.24, X13.25, X13.26, ZD8.C
PWR_IN2-: C111.2, K_PAR.11B, K_S2.2, R140.1, X15.17, X15.18, X15.19, X15.20, ZD9.A
PWR_SSTART: Q30.3, X16.4
Q4_OUT: Q4.S, R30.1, R32.2, R33.2, R36.2, ZD4.A
Q4_OUT1: Q31.S, R197.2, R199.2, R215.2, R271.1, ZD3.A
Q7C: Q10.B, Q10.C, Q11.B, Q13.C
Q7C1: Q33.C, Q36.B, Q36.C, Q37.B
Q9C: D13.C, Q9.2, Q9.4, ZD5.A
Q9C1: D37.C, Q35.2, Q35.4, ZD13.A
RTC_SELECT: IC26.6, MCU.8
SCLK: IC20.3, IC22.5, IC25.5, IC26.10, IC27.6, IC28.33, JP5.1, LCD1.36, MCU.ICSP_SCK
SENSE: IC1.10, Q1.3, R2.2
SENSE1: IC42.10, Q44.3, R236.2
SENSE1+: K_S1.4, X12.5, X12.5.1
SENSE1-: K_S1.5, X12.4, X12.4.1
SENSE1_IN+: K_S1.3, X13.22
SENSE1_IN-: K_S1.6, X13.21
SENSE2+: K_S2.5, X14.3, X14.3.1
SENSE2-: K_S2.4, X14.2, X14.2.1
SENSE2_IN+: K_S2.6, X15.22
SENSE2_IN-: K_S2.3, X15.21
SENSE+: C46.1, R37.2, R50.2, R93.1, X3.22
SENSE+1: C170.1, R178.2, R219.2, R257.1, X20.22
SENSE-: C52.1, R60.2, R62.1, R100.2, X3.21
SENSE-1: C172.1, R179.1, R220.2, R260.2, X20.21
SENSE_ERR: IC9.10, Q18.C, R98.1
SENSE_ERR1: IC37.10, Q49.C, R264.1
SENSE_PROT: Q11.C, Q12.C, Q16.C, R43.2, R51.2
SENSE_PROT1: Q37.C, Q38.C, Q48.C, R196.2, R213.2
SGND: C11.1, C21.2, C22.2, IC1.3, JP1.1, R7.2, R15.2, SH2.P$1
SGND1: C196.2, C197.2, C204.1, IC42.3, JP10.1, R230.2, R235.2, SH5.P$1
SW: C17.1, D5.3, L2.1, Q1.2, R4.1
SW1: C29.1, C33.1, D10.C, IC4.14, IC4.15, TR1.1
SW2: C87.1, C89.1, D19.C, IC16.14, IC16.15, L9.1
SW3: C193.1, D38.3, L16.1, Q44.2, R254.1
SW4: C214.1, C220.1, D40.C, IC43.14, IC43.15, TR3.1
SYNC: IC4.4, JP1.3, R21.1
SYNC1: IC22.2, IC34.7
SYNC2: IC23.2, IC34.1, IC34.2, IC34.3
SYNC3: IC43.4, JP10.3, R266.1
SYNC_MASTER: IC34.5, IC34.6, MCU.4, X16.7
TEMP_ANALOG: C128.2, MCU.A0, R144.1, X17.2
TEMP_FREQ1: IC30.3, R158.1
TEMP_NTC: NTC1.1, NTC1.1.1, X3.13
TEMP_NTC1: NTC2.1, NTC2.1.1, X20.13
TOCAP: C145.+, IC28.20
TOUCH_CS: LCD1.30, MCU.43
TOUCH_DIN: JP6.3, MCU.42
TOUCH_DOUT: JP7.3, MCU.3
TOUCH_IRQ: LCD1.34, MCU.2
TOUCH_SCLK: JP5.3, MCU.44
U_MON: IC6.7, R54.1, R55.1, R83.1
U_MON1: IC39.7, R181.1, R221.1, R267.1
U_SERVO: D15.C, D16.A, IC6.1, R57.2, R86.1
U_SERVO1: D31.A, D32.C, IC39.1, R206.1, R228.2
U_SET: IC11.4, IC13.4
U_SET1: IC35.4, IC46.4
U_SET_OUT: IC13.5, R52.1, R81.1
U_SET_OUT1: IC46.5, R180.1, R269.1
V+: C53.2, C54.1, C55.2, C56.2, C57.2, C66.1, C69.2, C82.2, FB2.P$2, IC6.8, IC7.8, IC8.7, IC10.2, IC11.1, IC12.6, IC13.2, IC15.3, R85.1, R89.2
V+1: C153.2, C163.1, C164.2, C169.2, C175.1, C181.2, C184.2, C185.2, FB9.P$2, IC35.1, IC38.7, IC39.8, IC40.8, IC41.2, IC46.2, IC47.6, IC48.3, R182.1, R205.2
V-: C58.2, C59.2, C60.1, C61.2, C62.2, C83.2, FB1.P$2, IC6.4, IC7.4, IC8.4, IC12.3, IC15.12, R102.1
V-1: C161.2, C174.2, C180.1, C182.2, C183.2, C186.2, FB8.P$2, IC38.4, IC39.4, IC40.4, IC47.3, IC48.12, R183.1
VIN: C97.1, D20.C, L8.1, TR2.7, X6.1
VOUT+: C35.1, C38.1, C39.1, IC4.11, L7.1, R19.1, TR1.3
VOUT+1: C209.1, C218.1, C219.1, IC43.11, L14.1, R243.1, TR3.3
VOUT-: D7.C, TR1.2
VOUT-1: D41.C, TR3.2
WATCHDOG: IC32.6, MCU.5
XUSB_GND: C100.2, C101.1, C103.2, FB6.P$2, IC18.1, IC19.2, IC19.8, X9.4, X11.4
XUSB_VBUS: C101.2, FB5.P$1, IC18.4, X11.1
